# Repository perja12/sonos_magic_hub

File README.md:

# Sonos Magic Hub

_UPDATE 2020-09-13:_ This workaround isn't needed anymore! Go to "device connector" in the menus of the LG TV and setup a new soundbar. When you come to the manufacturer selection you won't see Sonos listed, but if you use the search box and search for Sonos it will show up (I'm pretty sure it wasn't there before!). Now you should be able to control the Sonos Playbar with the remote when the TV is on.

Next step is to open the Sonos app (S1), go to the settings for the Playbar and follow the instructions for setting up a remote ("Remote Control Setup"). And voilà: you can now control the Playbar with the MagicRemote with TV both on and off.

This project contains firmware and hardware design files for using the LG Magic Remote that comes with LG OLED C9 TV with a Sonos Playbar. Sonos Playbar already has support for universal remotes, but the LG Magic Remote sends one set of codes when the TV is on and another set when the TV is off. So controlling the volume up, down and mute works fine when the TV is on, but not when it is off. It's not clear why LG has done it this way, but probably it is for controlling other LG devices.

Instead of waiting for LG to fix this I created a small circuit to translate the IR codes.

Note: there are various forum posts about the reverse problem for LG OLED CX. Apparently the Sonos Playbar can only be controlled by the LG remote when TV is off. This project doesn't solve that.

## How does it work?

This is straightforward: when a IR signal is received it will be converted to a code that the Sonos Playbar understands.

## List of IR codes

The table shows the IR codes sent by the remote when it is configured to send Philips RC6 codes as described here: https://support.sonos.com/s/article/3479?language=en

| Command     | IR code (TV off)         | IR code (TV on)    |
|-------------|--------------------------|--------------------|
| Volume up   | NEC, 20DF40BF, 32 bits   | RC6, 1010, 20 bits |
| Volume down | NEC, 20DFC03F, 32 bits   | RC6, 1011, 20 bits |
| Mute        | NEC, 0DF906F, 32 bits    | RC6, 100D, 20 bits |

## How to build the firmware

Use the Arduino IDE and install the ATTinyCore (https://github.com/SpenceKonde/ATTinyCore). Do this from Boards Manager in the IDE. Select "ATtiny 25/45/85" under boards and clock to 8 MHz (internal). For uploading the firmware I have used USBasp with Tag-Connect, but you can you use any way you prefer. Remember to burn the bootloader before uploading the firmware.

## Various notes

* Use this at your own risk! In the firmware I included support for NEC repeat code that the remote sends if one of the buttons are held down. There is a limit of 5 repeats in a row to avoid ramping up the volume too fast.
* There is no USB enumeration and thereby it is not according to the USB specifications. Still I think it should work fine with most USB hosts.
* It was unclear if the shield of the USB connector should be connected to GND or not. That is why I included R2. I left it unpopulated.
* The fuse (F1) is probably not needed. Maybe it should have some TVS diodes instead to suppress ESD.
* The IR library is from https://gist.github.com/SeeJayDee/caa9b5cc29246df44e45b8e7d1b1cdc5

## BOM

|Ref|Value         |Footprint                                                                 |
|---|--------------|--------------------------------------------------------------------------|
|C1 |10 uF         |Capacitor_Tantalum_SMD:CP_EIA-3528-12_Kemet-T_Pad1.50x2.35mm_HandSolder   |
|C2 |1 uF          |Capacitor_SMD:C_0805_2012Metric_Pad1.15x1.40mm_HandSolder                 |
|C3 |0.1 uF        |Capacitor_Tantalum_SMD:CP_EIA-3528-12_Kemet-T_Pad1.50x2.35mm_HandSolder   |
|C4 |0.1 uF        |Capacitor_SMD:C_0805_2012Metric_Pad1.15x1.40mm_HandSolder                 |
|D1 |LD271         |LED_THT:LED_D5.0mm_IRGrey                                                 |
|D2 |LED           |LED_SMD:LED_1206_3216Metric                                               |
|F1 |Polyfuse_Small|FUSM1812X02:FUSM1812X02                                                   |
|J1 |AVR-ISP-6     |(No actual part) Connector:Tag-Connect_TC2030-IDC-NL_2x03_P1.27mm_Vertical|
|J2 |629105136821  |(Micro USB connector) WE_629105136821:WE_629105136821                     |
|Q1 |MMBT3904      |Package_TO_SOT_SMD:SOT-23                                                 |
|R1 |1K            |Resistor_SMD:R_0805_2012Metric_Pad1.15x1.40mm_HandSolder                  |
|R2 |0             |Resistor_SMD:R_0805_2012Metric_Pad1.15x1.40mm_HandSolder                  |
|R3 |220           |Resistor_SMD:R_0805_2012Metric_Pad1.15x1.40mm_HandSolder                  |
|R4 |10K           |Resistor_SMD:R_0805_2012Metric_Pad1.15x1.40mm_HandSolder                  |
|R5 |220           |Resistor_SMD:R_0805_2012Metric_Pad1.15x1.40mm_HandSolder                  |
|R6 |35            |Resistor_SMD:R_0805_2012Metric_Pad1.15x1.40mm_HandSolder                  |
|U1 |ATtiny85V-10SU|Package_SO:SOIJ-8_5.3x5.3mm_P1.27mm                                       |
|U2 |TSOP38238     |OptoDevice:Vishay_MINICAST-3Pin                                           |

The PCB fits inside the Hammond 1551H (http://www.hammondmfg.com/pdf/1551H.pdf).

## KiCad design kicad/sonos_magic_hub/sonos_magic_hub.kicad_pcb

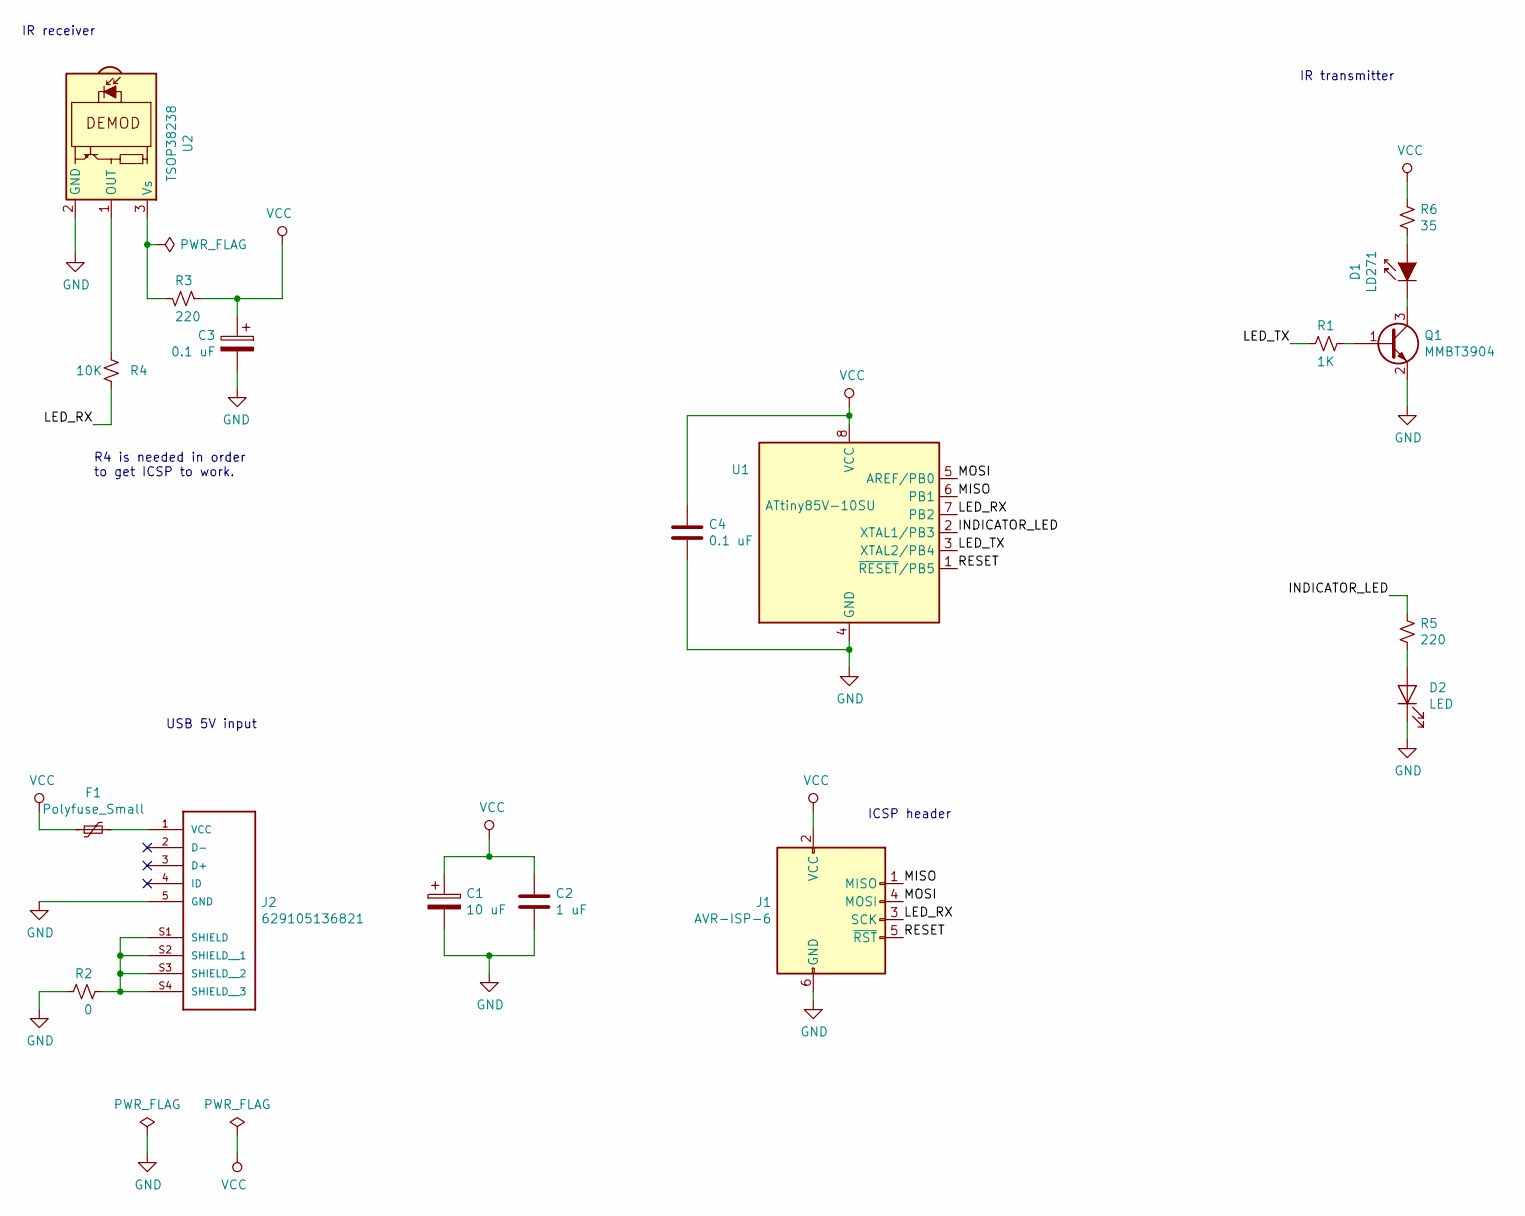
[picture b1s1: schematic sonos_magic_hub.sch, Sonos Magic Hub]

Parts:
C1: 10 uF; CP_EIA-3528-12_Kemet-T_Pad1.50x2.35mm_HandSolder
C2: 1 uF; C_0805_2012Metric_Pad1.15x1.40mm_HandSolder
C3: 0.1 uF; CP_EIA-3528-12_Kemet-T_Pad1.50x2.35mm_HandSolder
C4: 0.1 uF; C_0805_2012Metric_Pad1.15x1.40mm_HandSolder
D1: LD271; LED_D5.0mm_IRGrey
D2: LED; LED_1206_3216Metric
F1: Polyfuse_Small; FUSM1812X02
J1: AVR-ISP-6; Tag-Connect_TC2030-IDC-NL_2x03_P1.27mm_Vertical
J2: 629105136821; WE_629105136821
Q1: MMBT3904; SOT-23
R1: 1K; R_0805_2012Metric_Pad1.15x1.40mm_HandSolder
R2: 0; R_0805_2012Metric_Pad1.15x1.40mm_HandSolder
R3, R5: 220; R_0805_2012Metric_Pad1.15x1.40mm_HandSolder
R4: 10K; R_0805_2012Metric_Pad1.15x1.40mm_HandSolder
R6: 35; R_0805_2012Metric_Pad1.15x1.40mm_HandSolder
U1: ATtiny85V-10SU; SOIJ-8_5.3x5.3mm_P1.27mm
U2: TSOP38238; Vishay_MINICAST-3Pin

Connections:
/INDICATOR_LED: R5.1, U1.2 (XTAL1/PB3)
/LED_RX: J1.3 (SCK), R4.2, U1.7 (PB2)
/LED_TX: R1.1, U1.3 (XTAL2/PB4)
/MISO: J1.1 (MISO), U1.6 (PB1)
/MOSI: J1.4 (MOSI), U1.5 (AREF/PB0)
/RESET: J1.5 (~RST), U1.1 (~RESET~/PB5)
GND: C1.2, C2.2, C3.2, C4.2, D2.1 (K), J1.6 (GND), J2.5 (GND), Q1.2 (E), R2.1, U1.4 (GND), U2.2 (GND)
unnamed: D1.1 (K), Q1.3 (C)
unnamed: D1.2 (A), R6.2
unnamed: D2.2 (A), R5.2
unnamed: F1.2, J2.1 (VCC)
unnamed: J2.S1 (SHIELD), J2.S2 (SHIELD__1), J2.S3 (SHIELD__2), J2.S4 (SHIELD__3), R2.2
unnamed: Q1.1 (B), R1.2
unnamed: R3.2, U2.3 (Vs)
unnamed: R4.1, U2.1 (OUT)
VCC: C1.1, C2.1, C3.1, C4.1, F1.1, J1.2 (VCC), R3.1, R6.1, U1.8 (VCC)

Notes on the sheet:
ICSP header
IR receiver
IR transmitter
USB 5V input
R4 is needed in order to get ICSP to work.

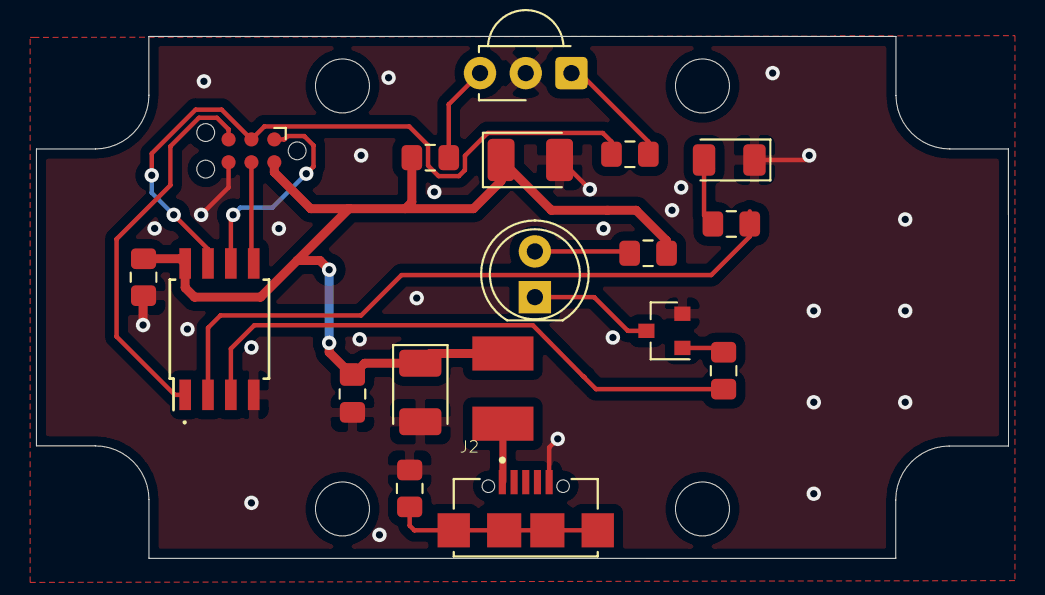
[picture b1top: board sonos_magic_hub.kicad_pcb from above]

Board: 2 copper layers, 54.0 x 29.0 mm, 18 parts (0 on the bottom side), 16 nets.

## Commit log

2020-09-13 Some small fixes.
2020-09-13 Update README. This workaround isn't needed anymore!
